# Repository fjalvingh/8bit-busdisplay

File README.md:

# 8-bit hex bus display board

This is a small display board which can be used to show the 8-bit
value on some bus on a 2 digit 7-segment display. The board uses an ATTINY1616
microcontroller which is dirt cheap and has 18 I/O pins. I need 9 for the display
(7x for a segment, 2x for selecting the digit) and 8 for input, so there's one
pin left which I will use to enable latching of the value if so desired.

I prototyped the thingy on a breadboard:

## Installing the prerequisite software (Linux/Ubuntu)

I do not use Windows (I hate and detest Microsoft) so for that you're on your own. I followed the instructions from here: [https://michael-crum.com/attiny1616/], many thanks to Michael!

Basically, you do:

```
sudo apt update
sudo apt install gcc-avr binutils-avr avr-libc gdb-avr avrdude
```
This should allow you to build the code with the usual 'make' command. This will do a build and also attempt to update the attiny using UPDI.

For that I used an USB to RS232 (5V) adapter and the following schematic:

* Red and black are the 5V pins from the Serial adapter
* White is the RX pin from the serial adapter
* Green is the TX pin from the serial adapter
* The resistor is 1K.

I used the following USB-to-Serial thing:

Do make sure that the jumper is set to 5V.

Once built you can test whether it can connect to the chip as follows:

```
sudo avrdude -c serialupdi -p t1616 -P "/dev/ttyUSB0" -b 57600
```
which should answer something like:
```
avrdude: AVR device initialized and ready to accept instructions
avrdude: device signature = 0x1e9421 (probably t1616)
```

## The schematic

Made in Kicad, the schematic diagram is very simple:

and the PCB is tiny:

I ordered the PCBs from [PCBWay](https://pcbway.com), and they offered to send me the boards for free in return for a review. Ordering the boards is very simple through their website - just upload the zip file with gerbers from Kicad. It gets even easier if you install the PCBWay plugin inside Kicad; with that the whole generation and upload process is done by the plugin, and you are left on the PCBWay page where you can further specify your needs for the PCB:

By default you get 5 boards, but you can of course change that amount to larger numbers. The price for these was $5, which is the price for most boards that do not exceed a certain size.

The boards are produced very quickly, and the process can be followed on the website which is quite nice. Most of the delay in getting them is in which kind of shipping you pick, and where you reside. I chose to pick the cheapest transport, "Global Direct Shipping" which was $4.21 for shipping to France. This made the total amount to be $10.93: $5 for the boards, $4.21 for shipping and the usual taxes. This is really cheap but of course you have to be patient because that shipping method takes a few weeks, 3 in my case. It can be a lot faster, of course, but you will pay accordingly; some of the more expensive options would let you get your boards a week after ordering.

The boards I received look really nice:

They look very clean and professional! It is amazing that you can get this for so low a price, and to have something that looks like it has been made by a professional instead of a hobbyist (well, they were of course made by a professional service, PCBWay). They also worked out of the box; the only issue I had was my own fault: the footprint of the 10uF capacitor was incorrect. I will have to change that. I worked around it by using a smaller cap. (2025/12/14 This should now be fixed on the PCB).

The components on the boards can be quite easily hand soldered. The microcontroller is quite large so with good eyes or good glasses you can easily position and solder a single corner and then align all pins correctly. Once that is done solder the other corner, check again the alignment and solder the rest. You can do this without having to do drag soldering; as long as your iron has a tip that is not too large all should be easy. You do need solder with good flux, or you need to apply some flux yourself though.

The smallest components are the two capacitors but a good set of pincers will make it easy.

Take care when soldering the pin headers; the large pin header is meant to go on the underside of the board! This is how the boards look when finished:

The next part is the programming part. I made a nice cable to be able to do that quickly:

Programming requires nothing else than connecting the cable to the new board:

and running the make file by entering 'make' inside the directory. This does the build and after that sends it to the board:

Immediately after you should see the board light up:

The boards are quite useful for debugging designs, I am using them with my experiment with old am2901 ALU chips:

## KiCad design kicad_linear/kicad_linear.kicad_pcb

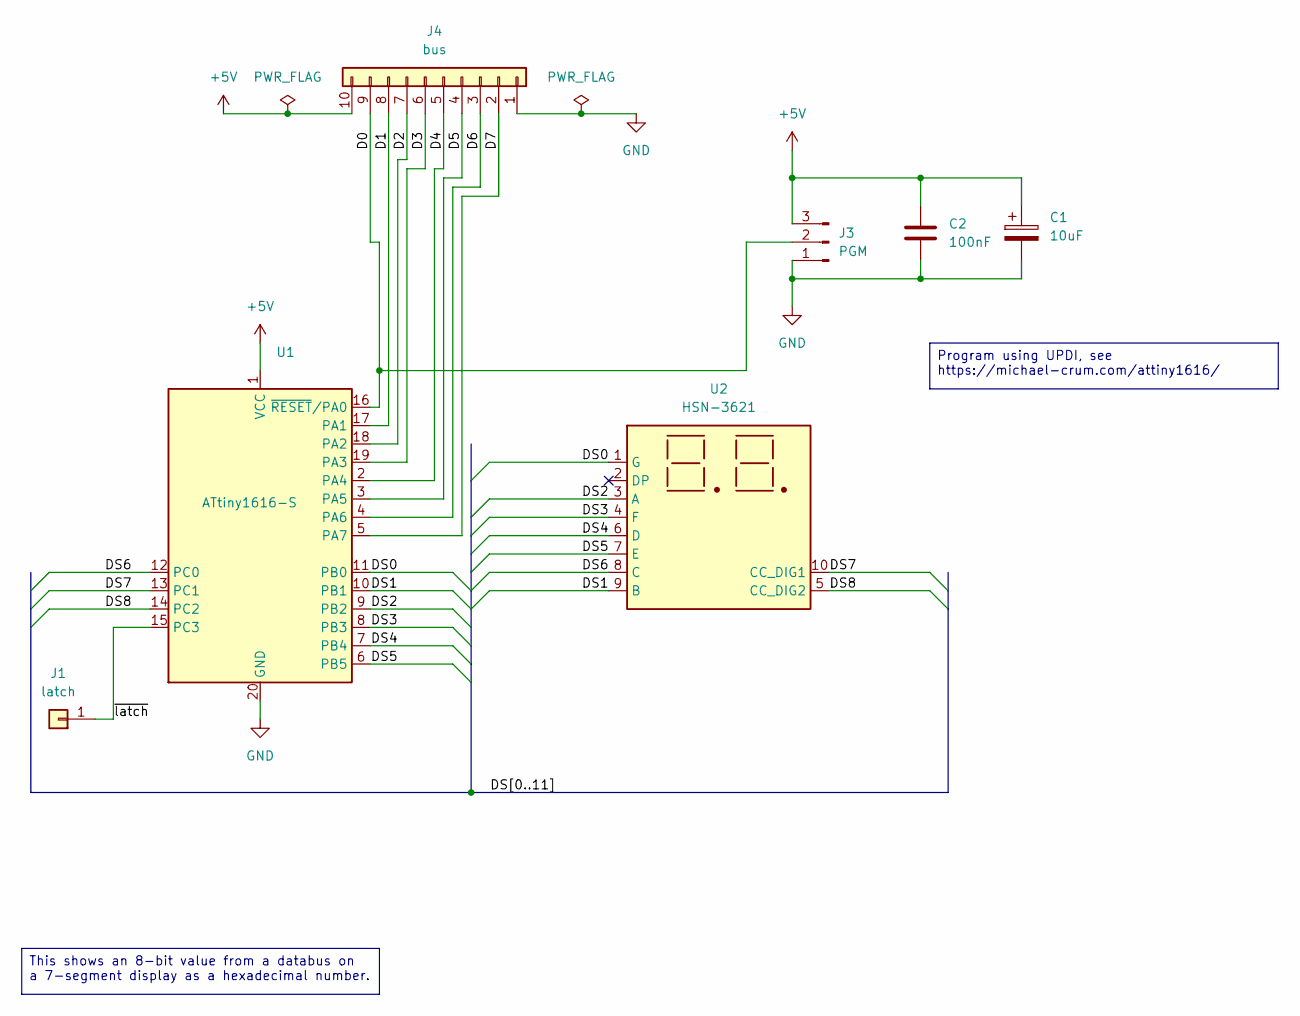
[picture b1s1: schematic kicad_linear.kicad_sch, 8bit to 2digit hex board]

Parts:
C1: 10uF; CP_EIA-3528-12_Kemet-T_HandSolder
C2: 100nF; C_0805_2012Metric_Pad1.18x1.45mm_HandSolder
J1: latch; PinHeader_1x01_P2.54mm_Vertical
J3: PGM; PinHeader_1x03_P2.54mm_Vertical
J4: bus; PinHeader_1x10_P2.54mm_Vertical
U1: ATtiny1616-S; SOIC-20W_7.5x12.8mm_P1.27mm
U2: HSN-3621

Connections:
+5V: C1.1, C2.1, J3.3, J4.10, U1.1 (VCC)
/D0: J3.2, J4.9, U1.16 (~RESET/PA0)
/D1: J4.8, U1.17 (PA1)
/D2: J4.7, U1.18 (PA2)
/D3: J4.6, U1.19 (PA3)
/D4: J4.5, U1.2 (PA4)
/D5: J4.4, U1.3 (PA5)
/D6: J4.3, U1.4 (PA6)
/D7: J4.2, U1.5 (PA7)
/DS0: U1.11 (PB0), U2.1 (G)
/DS1: U1.10 (PB1), U2.9 (B)
/DS2: U1.9 (PB2), U2.3 (A)
/DS3: U1.8 (PB3), U2.4 (F)
/DS4: U1.7 (PB4), U2.6 (D)
/DS5: U1.6 (PB5), U2.7 (E)
/DS6: U1.12 (PC0), U2.8 (C)
/DS7: U1.13 (PC1), U2.10 (CC_DIG1)
/DS8: U1.14 (PC2), U2.5 (CC_DIG2)
/~latch: J1.1, U1.15 (PC3)
GND: C1.2, C2.2, J3.1, J4.1, U1.20 (GND)

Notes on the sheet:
This shows an 8-bit value from a databus on a 7-segment display as a hexadecimal number.
Program using UPDI, see https://michael-crum.com/attiny1616/

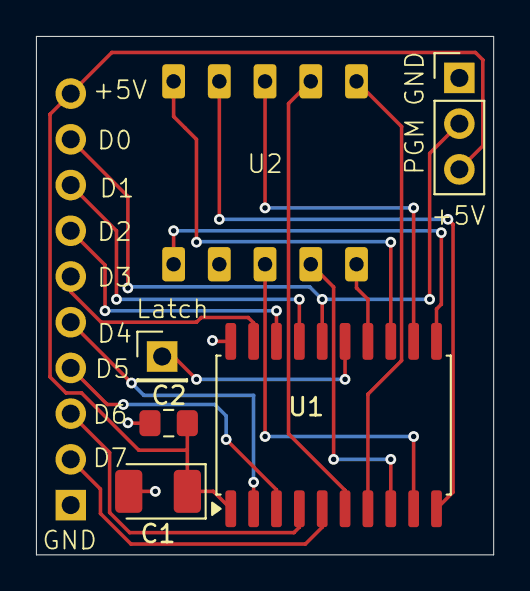
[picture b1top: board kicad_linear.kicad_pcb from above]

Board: 2 copper layers, 25.4 x 28.8 mm, 7 parts (1 on the bottom side), 20 nets.

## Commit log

2025-11-01 [kicad] Move symbols to project library
2025-11-01 Add programming details
2025-11-01 Add in-progress warning
2025-11-01 Add a linear variant that should be easier to use
2025-11-01 Finish docs so far
2025-11-01 Add serial device info
2025-12-07 Add actual result with PCBWay PCBs
2025-12-07 Minor text changes
2025-12-14 Fix capacitor footprint
2025-12-14 Comment on PCB being fixed.
